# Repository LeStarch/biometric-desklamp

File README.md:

# Fingerprint Controlled Biometric Desk Lamp
All the files required to build the finger-print enabled LED super lamp.

Files include Arduino code, KiCad files, etc.

## Functional Diagram

## 5V1A Power Supply
Used to power the Arduino and the cooling fan, this power supply is slightly under powered due to the narrow trace width between the components. Thus it is capible of supplying ~600mA. This is appears to be sufficient for the Teensy 3.2, finger-print scanner, and LED cooling fan.

**Needed improvments:** Trace widths need to be increased to reliably supply the advertised 1A power. 100k resistor should be replaced with surface mount equivalent.

## LED Driver
LEDs must be driven at a constant current (not voltage) in order to maximize their life expectancy. This driver produces a 1A constant ~30V supply for a high-powered LED module.  It is based on the Texas Instruments LM-3409 chip.  See: https://github.com/LeStarch/lm3409-calc for how the components were calculated.

**Needed Improvments:** 

Awaiting assembly.

**Issues Corrected in v2:** Trace widths may be too small to reliably cary 1A for LED driving. In practice, the lamp is stable, but trace widths should be increased in "an abundance of caution".

P-type MOSFET has a reversed layout and thus should be corrected in version 2.

## Nano Code (and now Teensy as well)
Code written using the Arduino libraries, which interfaces with the fingerprint reader and controls PWM signals used to drive the cooling fan and LED driver enable line.

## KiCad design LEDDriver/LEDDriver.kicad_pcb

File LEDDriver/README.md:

Kicad Files
===========

This directory contains the necessary schematic files, net, and pcb files for the Kicad design of the biometric desklamp.

Note: the 5v driver has been added as a sub-schematic

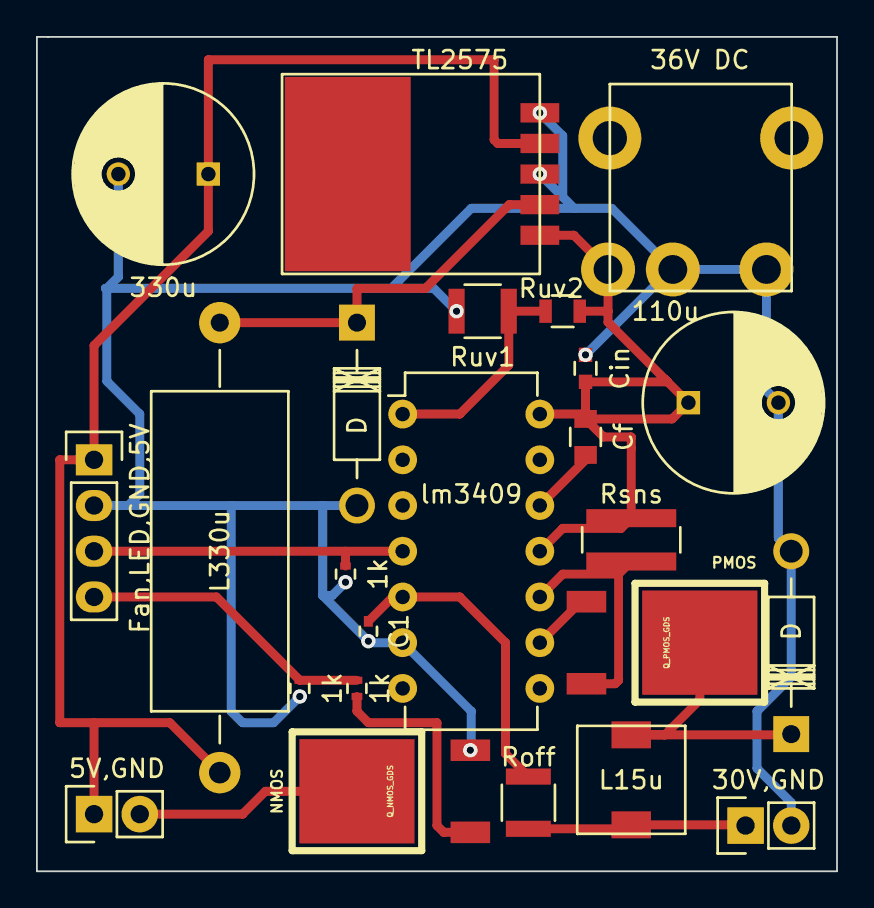
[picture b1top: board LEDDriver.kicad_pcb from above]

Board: 2 copper layers, 44.5 x 46.4 mm, 24 parts (0 on the bottom side), 15 nets.

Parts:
1k, 1k#2, 1k#3: R; R_0402
5V,GND: FanOut; Pin_Header_Straight_1x02
30V,GND: ToLED; Pin_Header_Straight_1x02
36V DC: 36V DC Power; PJ-051A
110u: CP; C_Radial_D10_L16_P5
330u: 330u; C_Radial_D10_L16_P5
C1: Coff; C_0402
Cf: Cf; C_0805
Cin: Cin; C_0603
D: D_Schottky; Diode_DO-41_SOD81_Horizontal_RM10
D#2: D_Schottky; Diode_DO-41_SOD81_Horizontal_RM10
Fan,LED,GND,5V: TeensyConnector; Pin_Header_Straight_1x04
L15u: INDUCTOR; SLF6045
L330u: 330u; Resistor_Horizontal_RM25mm
NMOS: Q_NMOS_GDS; TO-252-3
PMOS: Q_PMOS_GDS; TO-252-3
Roff: Roff; R_1210
Rsns: Rsns; R_1020
Ruv1: Ruv1; R_1210
Ruv2: Ruv2; R_0805
TL2575: TL25527; TO-263
lm3409: lm3409; DIP-14_W7.62mm

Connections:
/Regulator1/5VOut: 5V,GND.1, 330u.1, Fan,LED,GND,5V.1, L330u.2, TL2575.4
GND: 1k.2, 1k#3.2, 30V,GND.2, 36V DC.2, 36V DC.3, 110u.2, 330u.2, C1.2, Cin.2, D.2, D#2.2, Fan,LED,GND,5V.2, NMOS.3, Ruv1.2, TL2575.3, TL2575.5, lm3409.6
unnamed: C1.1, Roff.2, lm3409.5
unnamed: Cf.2, lm3409.12
unnamed: D.1, L15u.1, PMOS.2
unnamed: D#2.1, L330u.1, TL2575.2
unnamed: 30V,GND.1, L15u.2, Roff.1
unnamed: Ruv1.1, Ruv2.2, lm3409.1
unnamed: 1k#3.1, Fan,LED,GND,5V.3, lm3409.4
unnamed: PMOS.1, lm3409.9
unnamed: PMOS.3, Rsns.1, lm3409.10
unnamed: 5V,GND.2, NMOS.2
unnamed: 1k.1, 1k#2.1, Fan,LED,GND,5V.4
unnamed: 1k#2.2, NMOS.1
VCC: 36V DC.1, 110u.1, Cf.1, Cin.1, Rsns.2, Ruv2.1, TL2575.1, lm3409.11, lm3409.14

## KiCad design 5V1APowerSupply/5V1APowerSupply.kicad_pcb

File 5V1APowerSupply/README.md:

5V Driver
=========

This is now unused, as it was merged into a singleton board.

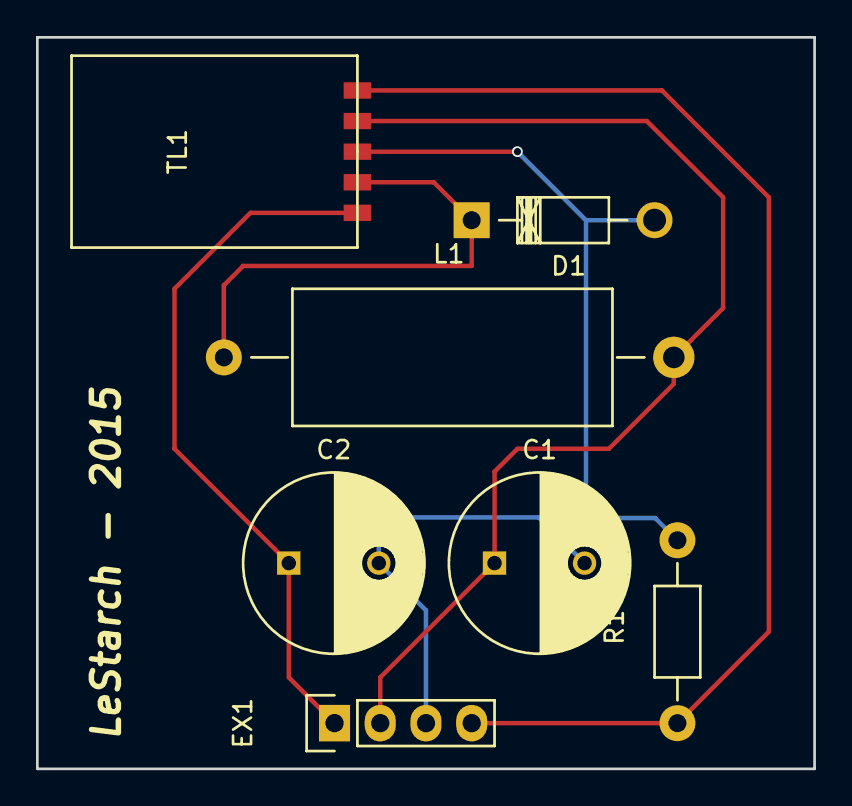
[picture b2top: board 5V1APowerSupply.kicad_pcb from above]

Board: 2 copper layers, 43.2 x 40.6 mm, 7 parts (0 on the bottom side), 5 nets.

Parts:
C1: 330u; C_Radial_D10_L16_P5
C2: 100u; C_Radial_D10_L16_P5
D1: D_Schottky; Diode_DO-41_SOD81_Horizontal_RM10
EX1: Conn; Pin_Header_Straight_1x04
L1: 330u; Resistor_Horizontal_RM25mm
R1: 100k; Resistor_Horizontal_RM10mm
TL1: TL25527; TO-263

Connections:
unnamed: C1.1, EX1.2, L1.2, TL1.4
unnamed: C1.2, C2.2, D1.2, EX1.3, R1.2, TL1.3
unnamed: C2.1, EX1.1, TL1.1
unnamed: D1.1, L1.1, TL1.2
unnamed: EX1.4, R1.1, TL1.5

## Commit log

2014-12-02 Adding initial file
2014-12-03 Fully functioning prototype. NO ERROR HANDLING
2015-05-17 Toggle
2015-11-27 lestarch: assembling LED driver, 5V 1A power supply, and fingerprint code.
2015-11-27 Explanation in the README.
2016-01-16 lestarch: working prototype code
2016-01-30 lestarch: computer failure, rats abandon ship
2016-05-07 lestarch: aparently capture needs to be called
2016-09-06 lestarch: adding design files for combined design v2.0
2016-10-09 header file for command handling
2016-10-09 partial implementation of command.cpp
2016-10-15 lestarch: working rewritten software
2016-10-15 lestarch: fixing fan/led output
2016-10-15 lestarch: changing resistors to pulldown resistors; adding pulldown to LED
2016-10-15 lestarch: adding better readmes
2020-02-04 lestarch: saving last backup
2023-02-25 adding led potentionmeter code
